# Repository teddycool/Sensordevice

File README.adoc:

# Sensordevice

A simple generic circuit with example software for a battery powered ESP8266-07.
The circuit can handle one-wire, DHTs and all kinds of I2C sensors. It has capabillities to measures the status of the battery to know  when charging or replacement is needed. The hardware has all pull-ups and pull-downs needed for the different interfaces as well as an onewire tempsensor and an i2c HSM circuit. 

# The Hardware:

The device hardware comes in two flavours:

HW7.1 (left): Powered by 1 1500mAh LiPo and have a built-in charger. Perfect for sensors where charging now and then is an option. The circuitboard is optimised for a FB-29 box

HW8.2 (right): Powered by 3 AAA alkaline batteries. Perfect for sensors that should have a long life-time without battery change and measures rather seldom. The circuitboard is optimised for a FB-29 box.

Since everything will fit i a small enclosure and can be used without any external power supply for long a time, it is well suited for different small sensors or IoT devices. 

image::20200407_090953.jpg[Hardware version 7 and 8]

Hardware 7 and 8.

image::20200407_091215.jpg[]

Hardware 8 in a FB-29 box

There is a also a start for HW9 wich is intended for a power-supply using one AA battery and a 'booster' for ultra low losses. It's a work in (slow) progress so far...

# Software:
Example of software for a device using 2 one-wire temperature gauges and sends information to backend each hour.

## Backend:
Example of html, php, json and sql needed to create some charts with the data.
Data is inserted in a database table using a simple php script, extracted and mangled to json in an other php script and drawn with google chart javascript in the html file.

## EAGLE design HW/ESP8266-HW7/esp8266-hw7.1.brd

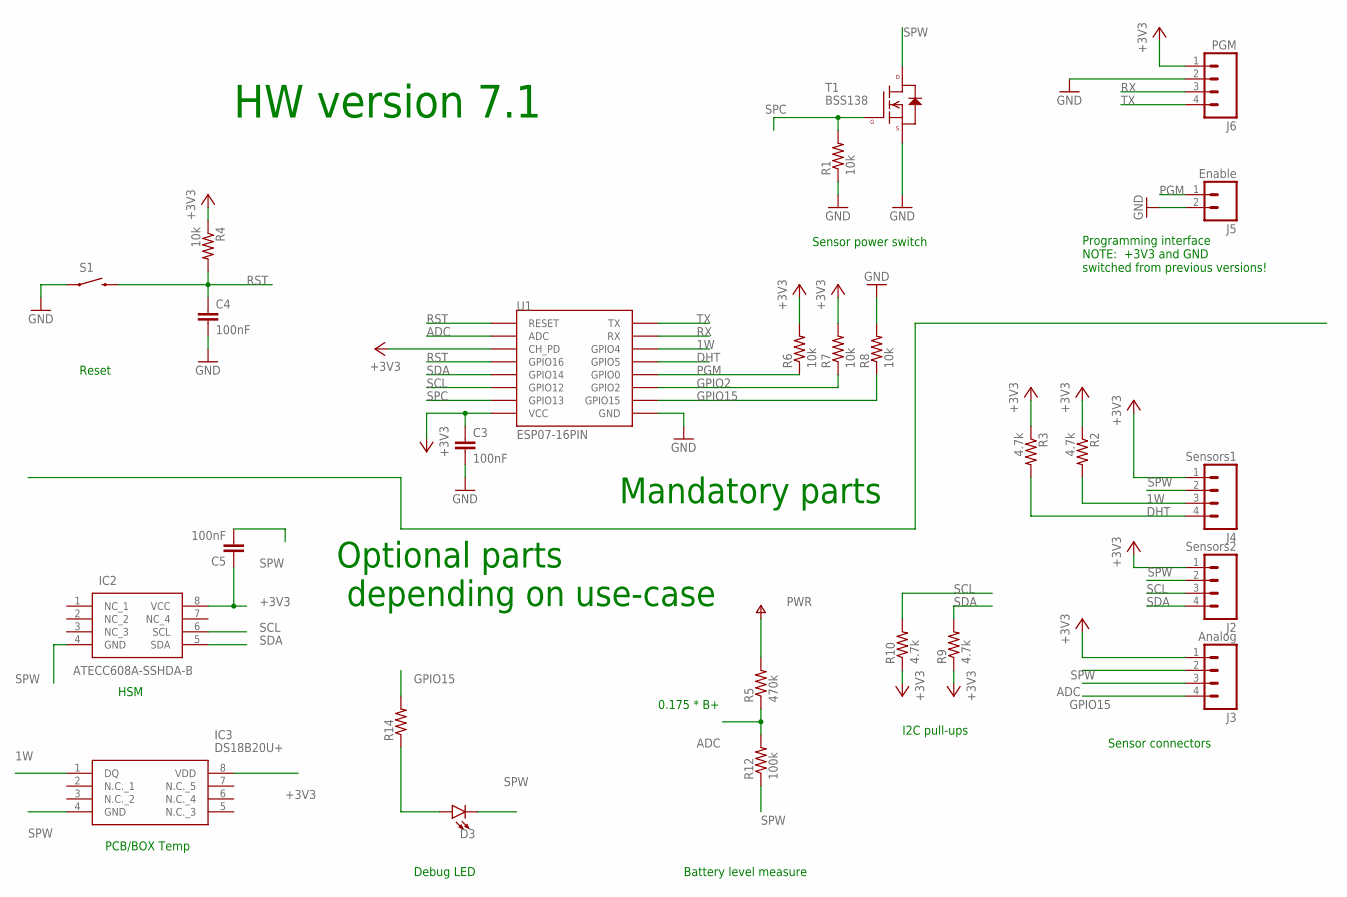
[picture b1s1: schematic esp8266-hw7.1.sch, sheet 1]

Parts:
C3, C4, C5: 100nF; 0805
D3: LED3MM; LED_3MM
IC2: ATECC608A-SSHDA-B; SOIC127P600X175-8N
IC3: DS18B20U+; SOP65P490X110-8N
J2: Sensors2; 1X04
J3: Analog; 1X04
J4: Sensors1; 1X04
J5: Enable; 1X02
J6: PGM; 1X04
R1, R4, R6, R7, R8: 10k; 0805
R2, R3, R9, R10: 4.7k; 0805
R5: 470k; 0805
R12: 100k; 0805
R14: 470; 0805
S1: RESET; TACTILE-SWITCH-1101NE
T1: BSS138; SOT23-3
U1: ESP07-16PIN

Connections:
1W: IC3.1 (DQ), J4.3, R2.2, U1.GPIO4
+3V3: C3.1, C5.1, IC2.8 (VCC), IC3.8 (VDD), J2.1, J3.1, J4.1, J6.1, R2.1, R3.1, R4.1, R6.2, R7.2, R9.1, R10.1, U1.CH_PD, U1.VCC; also elsewhere on the board
ADC: J3.3, R5.1, R12.2, U1.ADC
DHT: J4.4, R3.2, U1.GPIO5
GND: C3.2, C4.2, J5.2, J6.2, R1.1, R8.2, S1.1, T1.2 (S), U1.GND; also elsewhere on the board
GPIO2: R7.1, U1.GPIO2
GPIO15: J3.4, R8.1, R14.2, U1.GPIO15
unnamed: D3.A, R14.1
PGM: J5.1, R6.1, U1.GPIO0
PWR: R5.2; also elsewhere on the board
RST: C4.1, R4.2, S1.2, U1.GPIO16, U1.REST (RESET)
RX: J6.3, U1.RX
SCL: IC2.6 (SCL), J2.3, R10.2, U1.GPIO12
SDA: IC2.5 (SDA), J2.4, R9.2, U1.GPIO14
SPC: R1.2, T1.1 (G), U1.GPIO13
SPW: C5.2, D3.K (C), IC2.4 (GND), IC3.4 (GND), J2.2, J3.2, J4.2, R12.1, T1.3 (D)
TX: J6.4, U1.TX

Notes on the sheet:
0.175 * B+
Reset
Debug LED
Battery level measure
Sensor power switch
Sensor connectors
I2C pull-ups
Programming interface NOTE: +3V3 and GND switched from previous versions!
HSM
HW version 7.1
PCB/BOX Temp
Mandatory parts
Optional parts depending on use-case

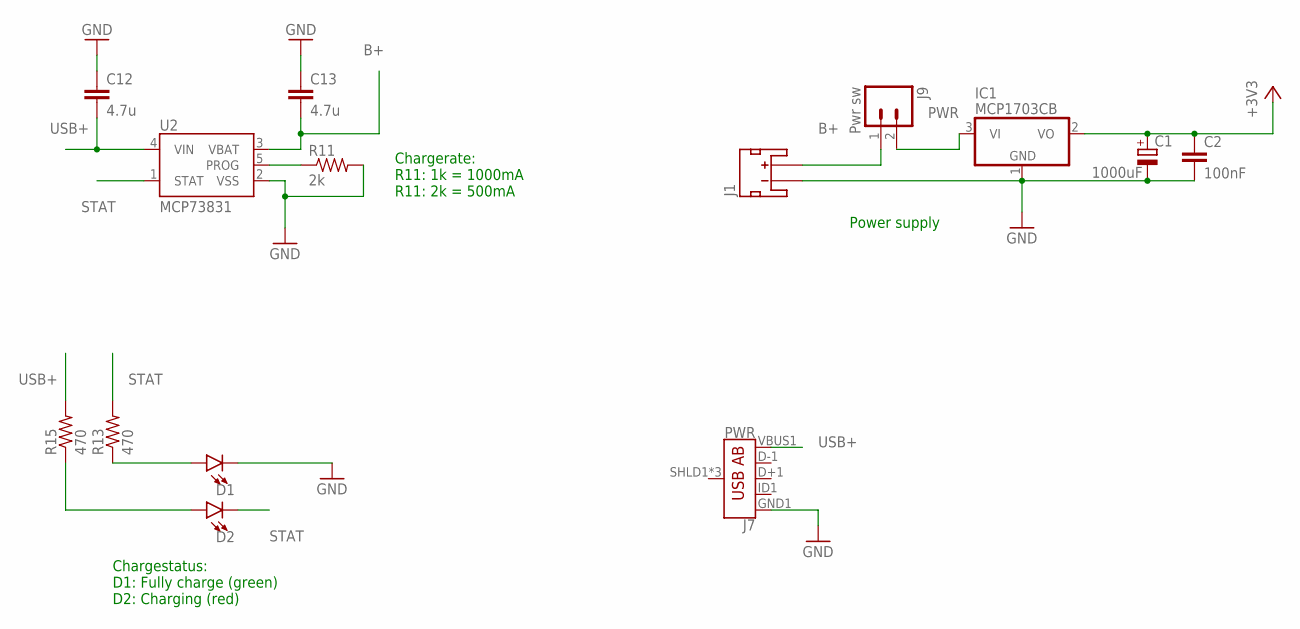
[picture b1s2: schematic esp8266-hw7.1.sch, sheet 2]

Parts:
C1: 1000uF; E3,5-8
C2: 100nF; 0805
C12, C13: 4.7u; 0805
D1, D2: LED3MM; LED_3MM
IC1: MCP1703CB; SOT23
J1: J1; JST-2-SMD
J7: PWR; USB-AB-MICRO-SMD
J9: Pwr sw; 1X02
R11: 2k; 0805
R13, R15: 470; 0805
U2: MCP73831; SOT23-5

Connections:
+3V3: C1.+, C2.1, IC1.2 (VO); also elsewhere on the board
B+: C13.2, J1.2 (+), J9.1, U2.3 (VBAT)
GND: C1.-, C2.2, C12.1, C13.1, D1.K (C), IC1.1 (GND), J1.1 (-), J7.GND1 (GND), R11.2, U2.2 (VSS); also elsewhere on the board
unnamed: D1.A, R13.1
unnamed: D2.A, R15.1
unnamed: R11.1, U2.5 (PROG)
PWR: IC1.3 (VI), J9.2; also elsewhere on the board
STAT: D2.K (C), R13.2, U2.1 (STAT)
USB+: C12.2, J7.VBUS1 (VBUS), R15.2, U2.4 (VIN)

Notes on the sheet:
Power supply
Chargerate: R11: 1k = 1000mA R11: 2k = 500mA
Chargestatus: D1: Fully charge (green) D2: Charging (red)

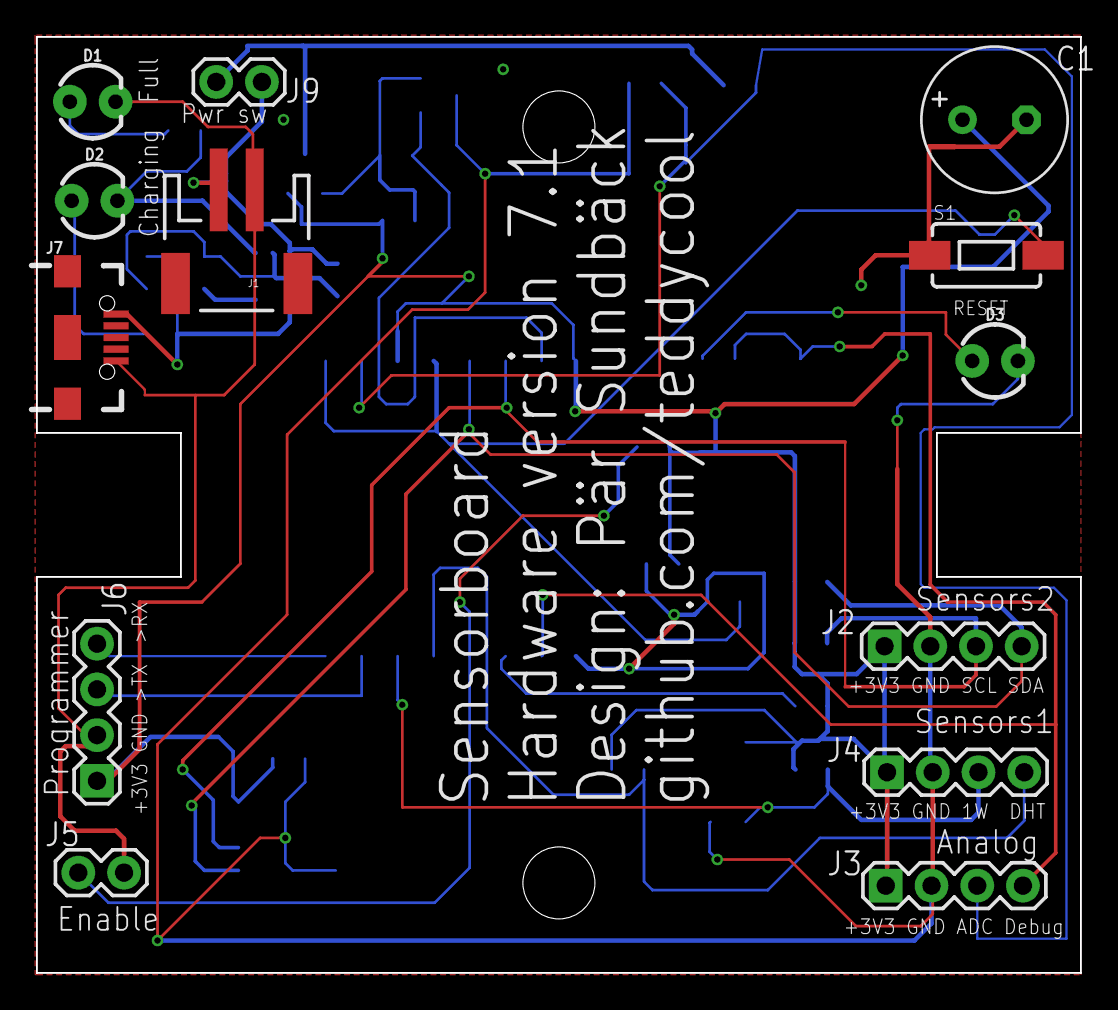
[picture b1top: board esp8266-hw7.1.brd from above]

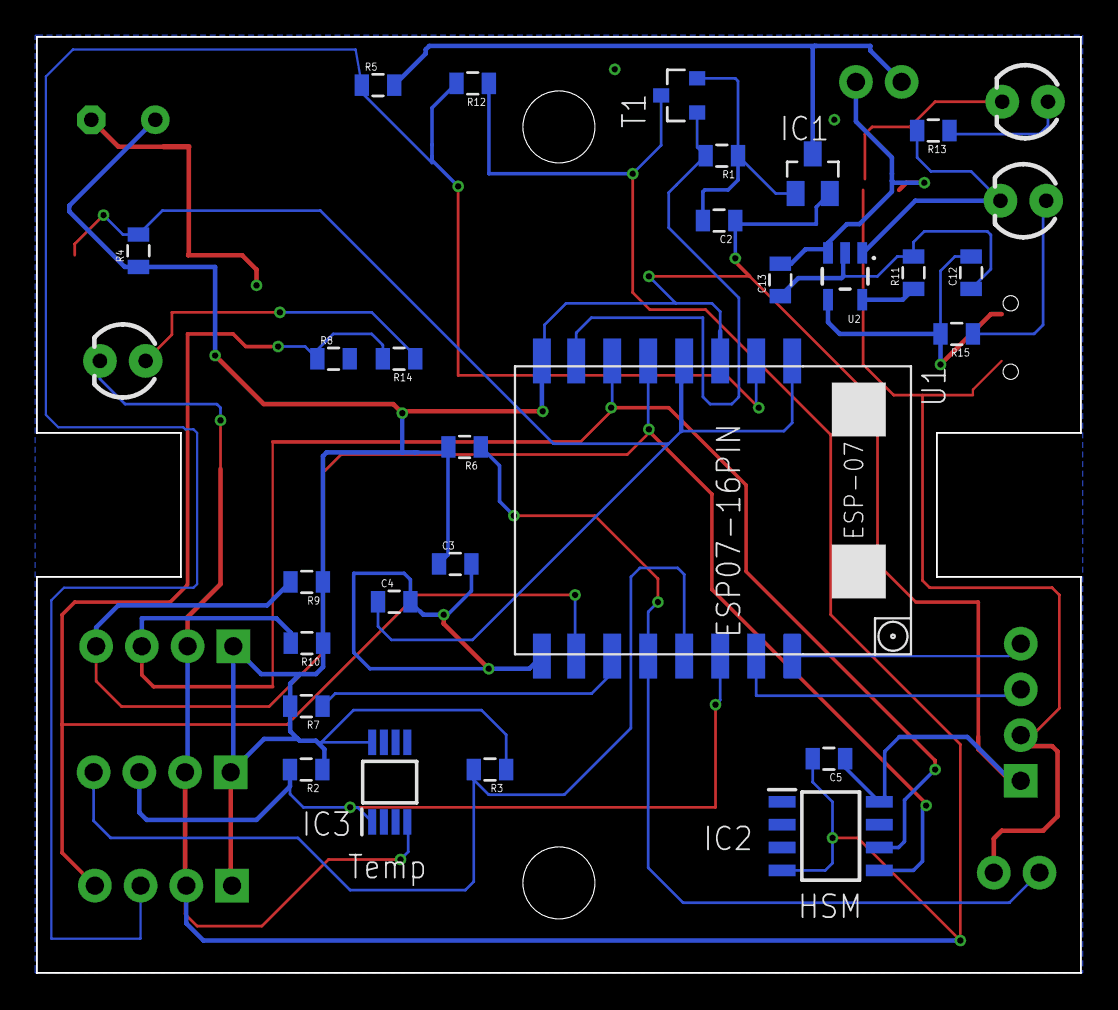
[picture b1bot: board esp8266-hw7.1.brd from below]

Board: 2 copper layers, 58.0 x 52.0 mm, 40 parts (27 on the bottom side), 23 nets.

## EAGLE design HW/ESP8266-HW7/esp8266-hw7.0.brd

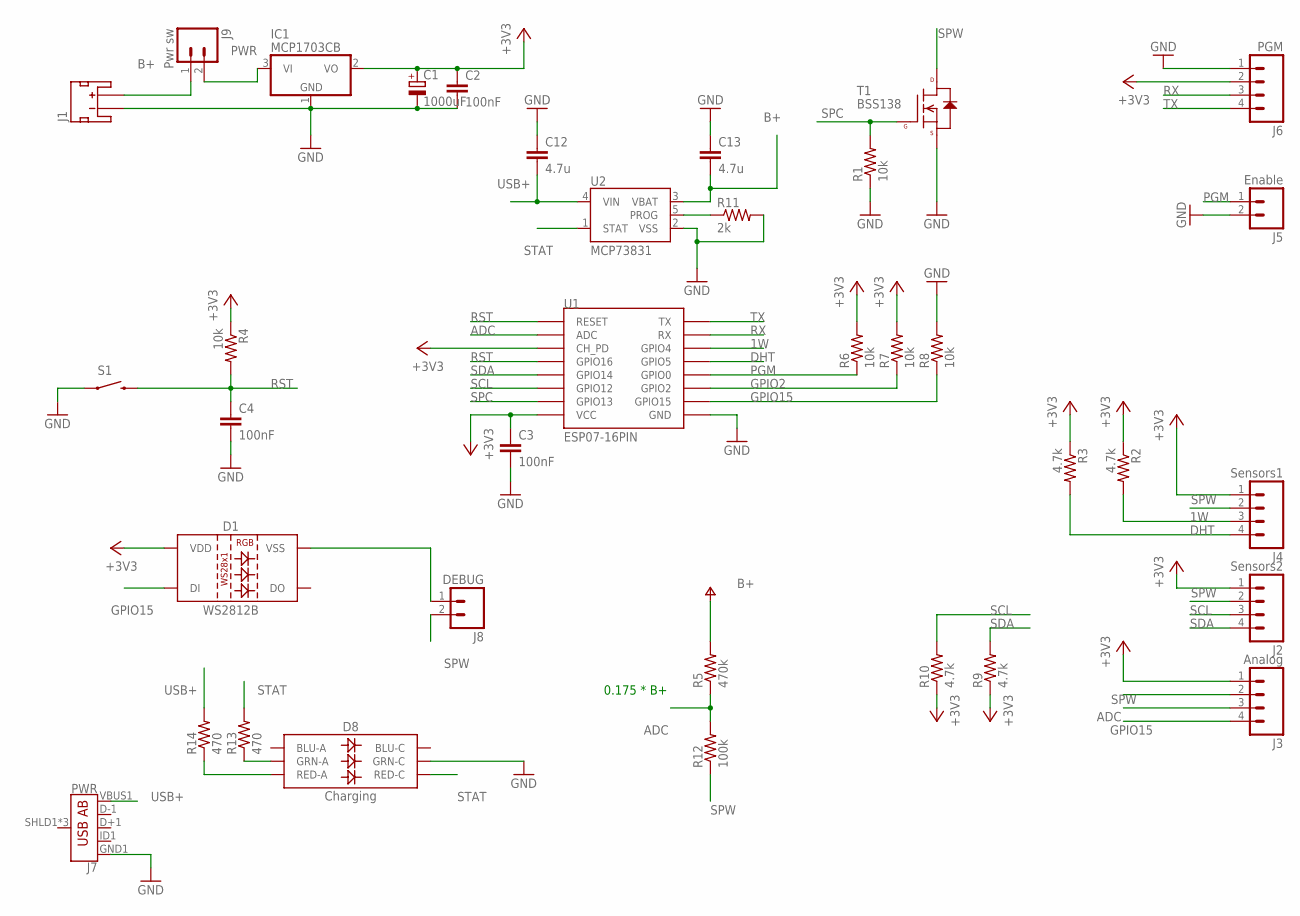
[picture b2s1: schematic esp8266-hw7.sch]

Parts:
C1: 1000uF; E3,5-8
C2, C3, C4: 100nF; 0805
C12, C13: 4.7u; 0805
D1: WS2812B
D8: Charging; LED-TRICOLOR-5050
IC1: MCP1703CB; SOT23
J1: J1; JST-2-SMD
J2: Sensors2; 1X04
J3: Analog; 1X04
J4: Sensors1; 1X04
J5: Enable; 1X02
J6: PGM; 1X04
J7: PWR; USB-AB-MICRO-SMD
J8: DEBUG; 1X02
J9: Pwr sw; 1X02
R1, R4, R6, R7, R8: 10k; 0805
R2, R3, R9, R10: 4.7k; 0805
R5: 470k; 0805
R11: 2k; 0805
R12: 100k; 0805
R13, R14: 470; 0805
S1: RESET; TACTILE-SWITCH-1101NE
T1: BSS138; SOT23-3
U1: ESP07-16PIN
U2: MCP73831; SOT23-5

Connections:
1W: J4.3, R2.2, U1.GPIO4
+3V3: C1.+, C2.1, C3.1, D1.1 (VDD), IC1.2 (VO), J2.1, J3.1, J4.1, J6.2, R2.1, R3.1, R4.1, R6.2, R7.2, R9.1, R10.1, U1.CH_PD, U1.VCC
ADC: J3.3, R5.1, R12.2, U1.ADC
B+: C13.2, J1.2 (+), J9.1, R5.2, U2.3 (VBAT)
DHT: J4.4, R3.2, U1.GPIO5
GND: C1.-, C2.2, C3.2, C4.2, C12.1, C13.1, D8.6 (GRN-C), IC1.1 (GND), J1.1 (-), J5.2, J6.1, J7.GND1 (GND), R1.1, R8.2, R11.2, S1.1, T1.2 (S), U1.GND, U2.2 (VSS)
GPIO2: R7.1, U1.GPIO2
GPIO15: D1.4 (DI), J3.4, R8.1, U1.GPIO15
unnamed: D8.1 (GRN-A), R13.1
unnamed: D1.3 (VSS), J8.1
unnamed: D8.2 (RED-A), R14.1
unnamed: R11.1, U2.5 (PROG)
PGM: J5.1, R6.1, U1.GPIO0
PWR: IC1.3 (VI), J9.2
RST: C4.1, R4.2, S1.2, U1.GPIO16, U1.REST (RESET)
RX: J6.3, U1.RX
SCL: J2.3, R10.2, U1.GPIO12
SDA: J2.4, R9.2, U1.GPIO14
SPC: R1.2, T1.1 (G), U1.GPIO13
SPW: J2.2, J3.2, J4.2, J8.2, R12.1, T1.3 (D)
STAT: D8.5 (RED-C), R13.2, U2.1 (STAT)
TX: J6.4, U1.TX
USB+: C12.2, J7.VBUS1 (VBUS), R14.2, U2.4 (VIN)

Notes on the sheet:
0.175 * B+

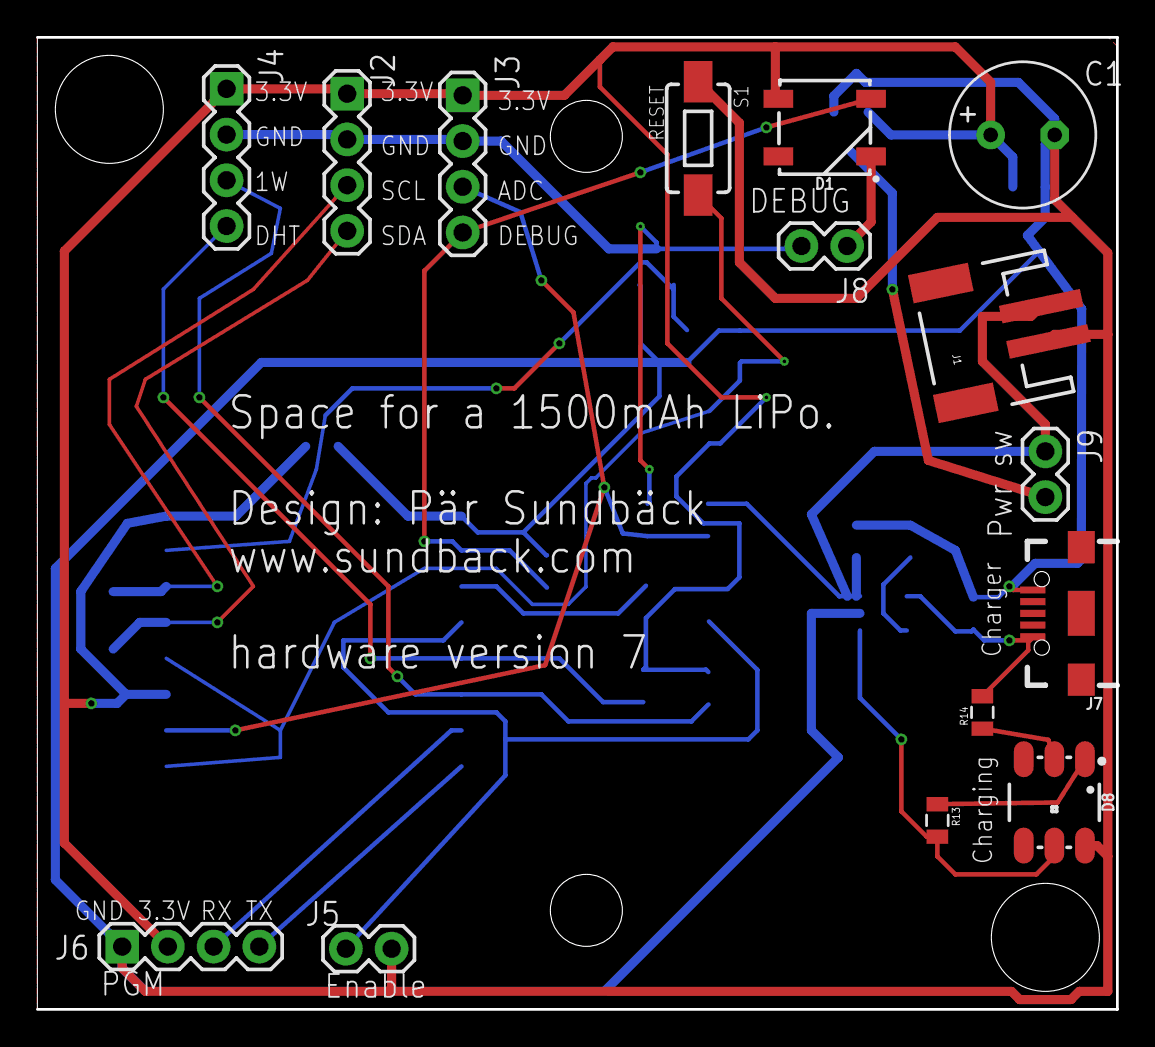
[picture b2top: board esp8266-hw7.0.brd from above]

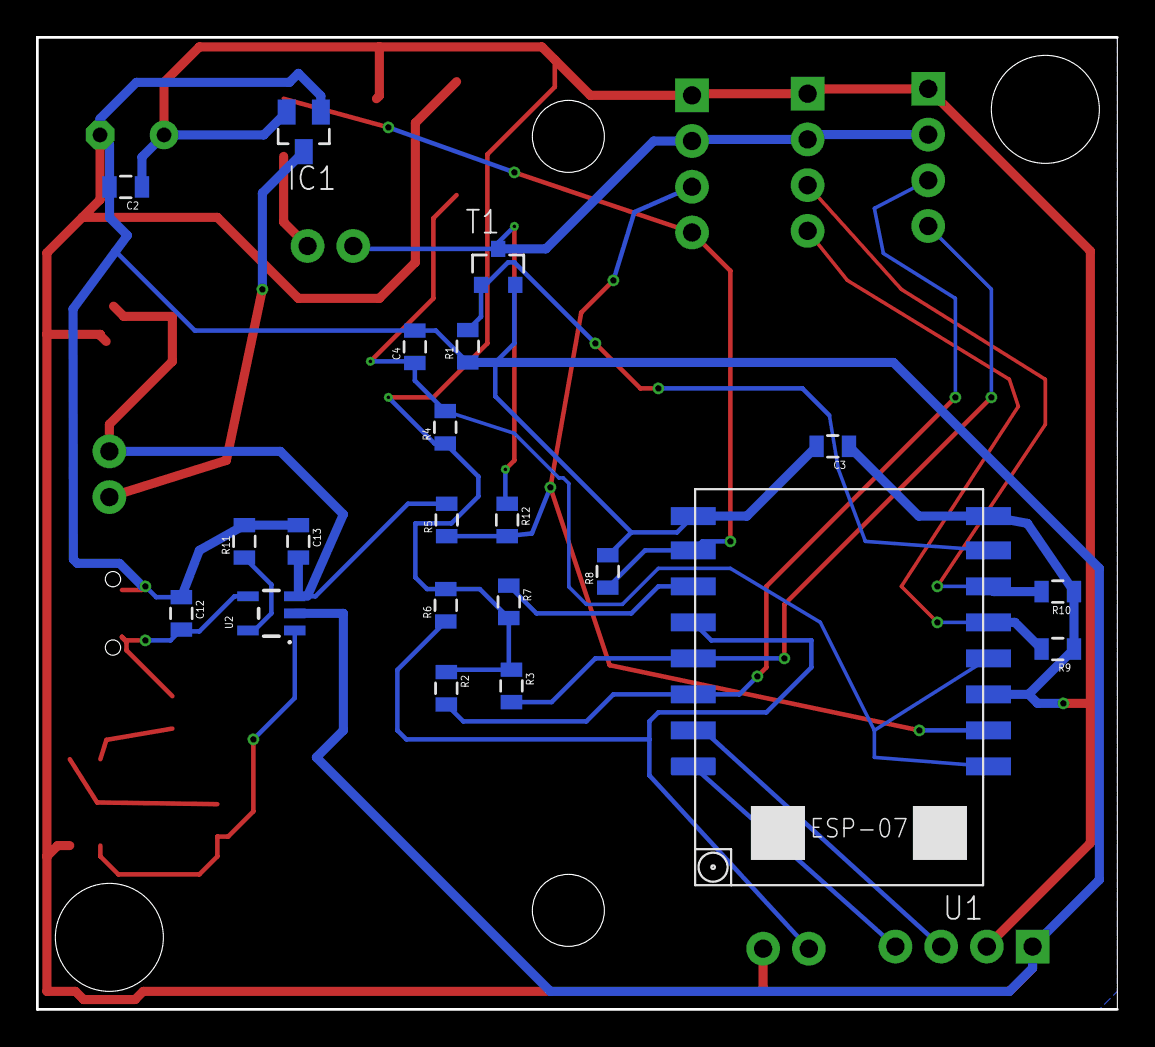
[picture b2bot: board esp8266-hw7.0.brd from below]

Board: 2 copper layers, 60.0 x 54.0 mm, 36 parts (21 on the bottom side), 23 nets.

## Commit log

2019-10-26 First commit
    New repo, first commit
2020-04-07 New pcb releases and some updated software
    New (final?) releases of pcbs for version 7 and 8. New test program to run for test of the built hardware.

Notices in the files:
parts and their libraries:
SparkFun-Passives: Licensing: Creative Commons ShareAlike 4.0 International - https://creativecommons.org/licenses/by-sa/4.0
